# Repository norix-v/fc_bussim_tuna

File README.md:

# FC Cartridge bus simulator "tuna"

## What's it this?

This is famicom cartridge bus simulator 'kazzo' compatible hardware and extra software.  
The original project is [here](https://ja.osdn.net/projects/unagi/).  

## How to use

This data is provided "as is" and is freely available as long as you comply with the license.  
The author does not give an explanation or answer.  

## 何これ？

このプロジェクトはfamicom bus simulator 'kazzo' の互換のハードウェアとおまけのソフトウェアです。  
オリジナルのプロジェクトは[こちら](https://ja.osdn.net/projects/unagi/)です。  

## 使い方

このデータは"現状のまま"で提供され、ライセンスを遵守する限りにおいて自由に使用出来ます。なお、作者は説明も回答も致しませんのであしからず。

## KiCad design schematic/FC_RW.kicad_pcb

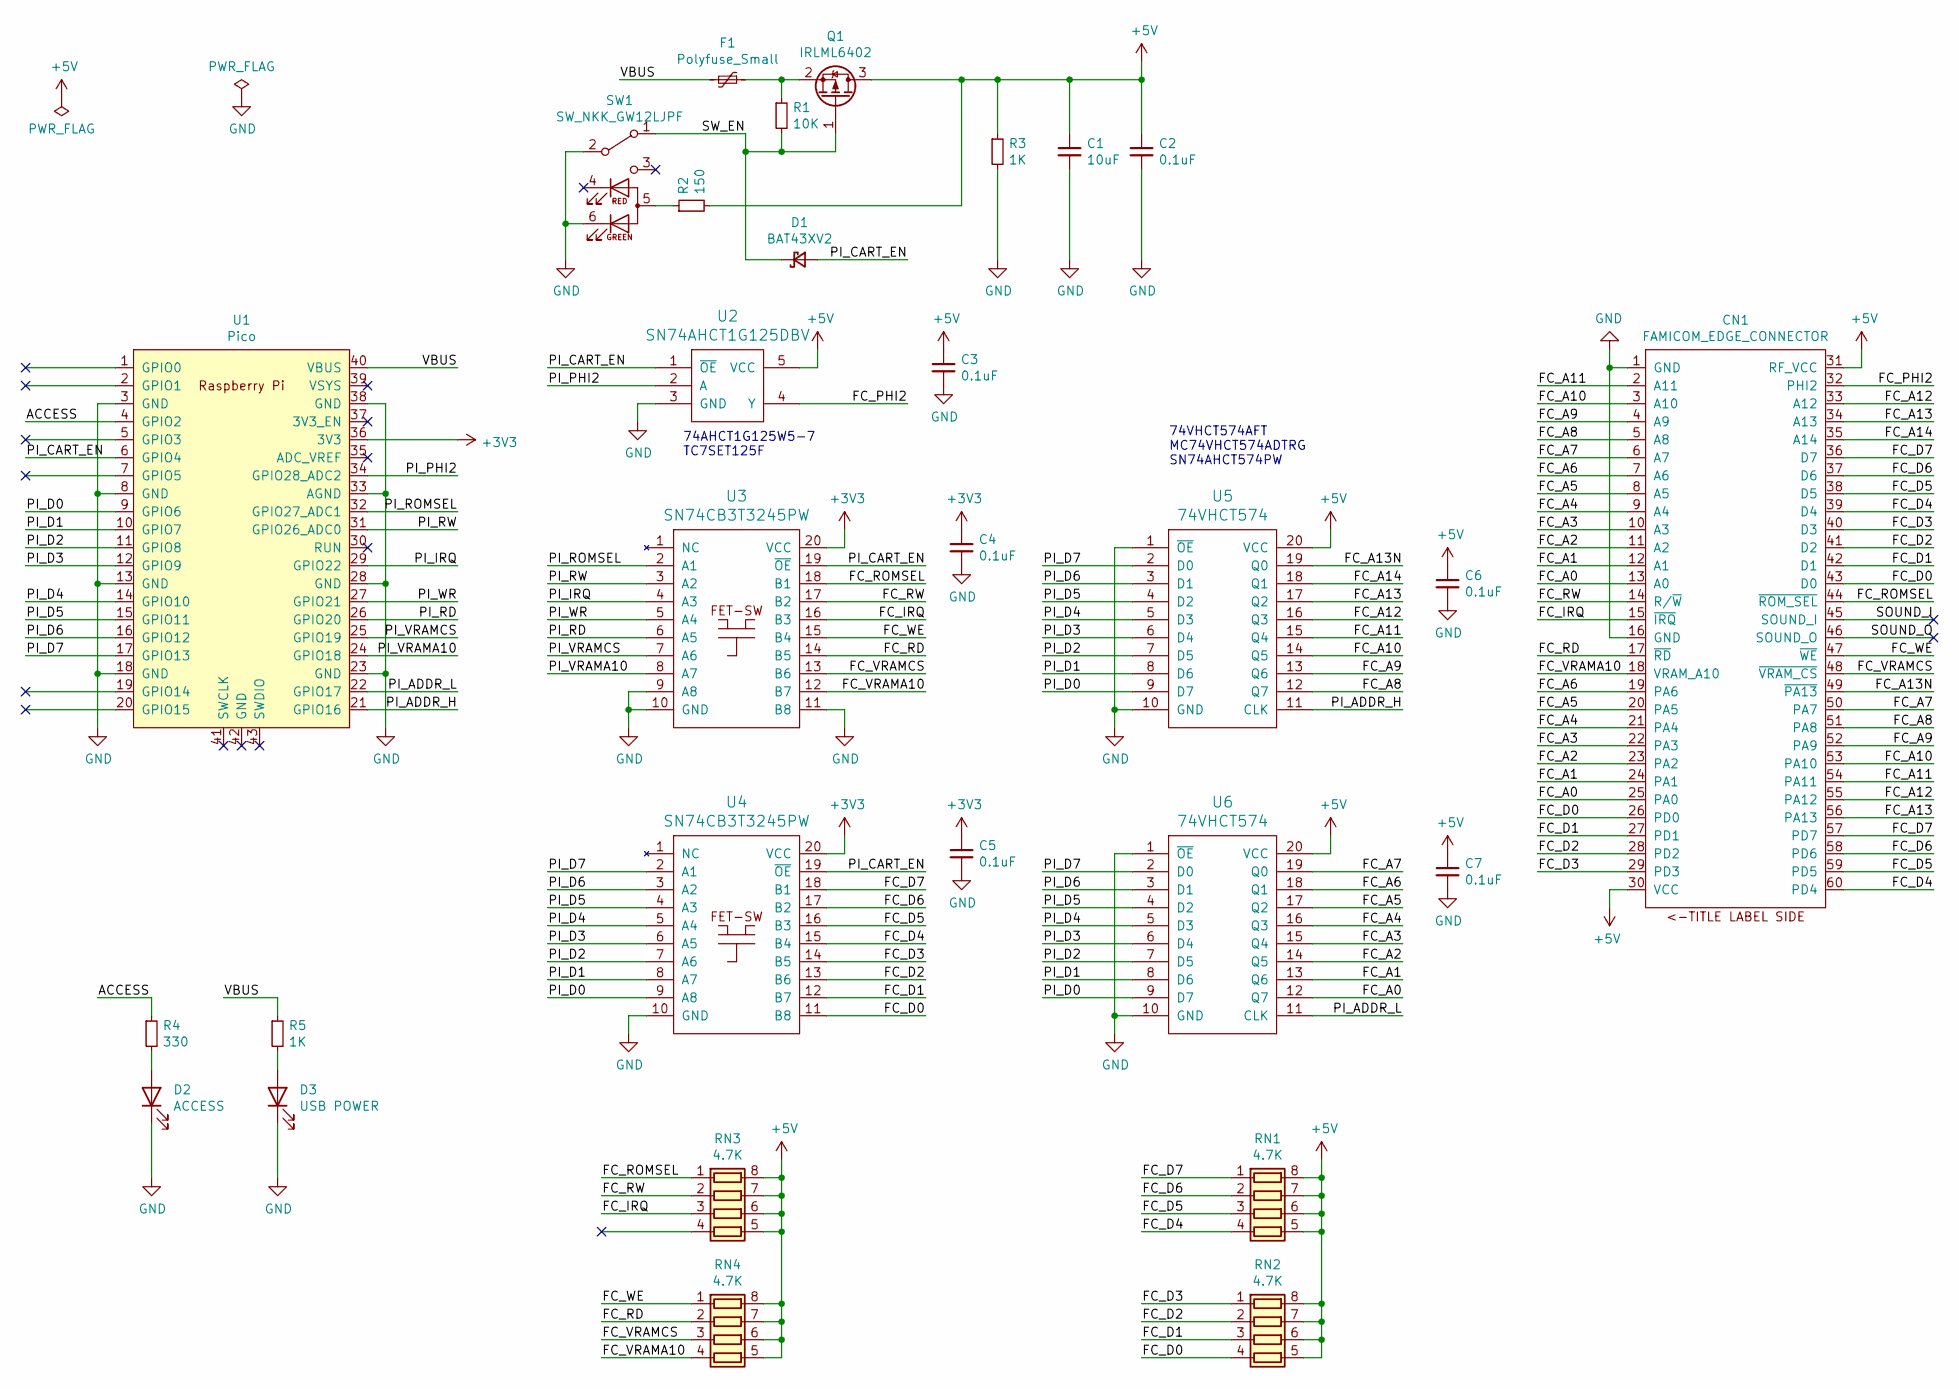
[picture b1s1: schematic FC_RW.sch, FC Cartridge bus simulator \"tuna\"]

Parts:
C1: 10uF; C_0805_2012Metric
C2, C3, C4, C5, C6, C7: 0.1uF; C_0603_1608Metric
CN1: FAMICOM_EDGE_CONNECTOR; Famicom_60pin
D1: BAT43XV2; D_SOD-523
D2: ACCESS; D_0805_2012Metric
D3: USB POWER; D_0805_2012Metric
F1: Polyfuse_Small; Fuse_0805_2012Metric
Q1: IRLML6402; SOT-23
R1: 10K; R_0603_1608Metric
R2: 150; R_0603_1608Metric
R3, R5: 1K; R_0603_1608Metric
R4: 330; R_0603_1608Metric
RN1, RN2, RN3, RN4: 4.7K; R_Array_Convex_4x0603
SW1: SW_NKK_GW12LJPF; SW_NKK_GW12LJP
U1: Pico; RPi_Pico_SMD_TH
U2: SN74AHCT1G125DBV; SOT-23-5
U3, U4: SN74CB3T3245PW; TSSOP-20_4.4x6.5mm_P0.65mm
U5, U6: 74VHCT574; TSSOP-20_4.4x6.5mm_P0.65mm

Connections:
+3V3: C4.1, C5.1, U1.36 (3V3), U3.20 (VCC), U4.20 (VCC)
+5V: C1.1, C2.1, C3.1, C6.1, C7.1, CN1.30 (VCC), CN1.31 (RF_VCC), Q1.3 (D), R2.2, R3.1, RN1.5 (R4.2), RN1.6 (R3.2), RN1.7 (R2.2), RN1.8 (R1.2), RN2.5 (R4.2), RN2.6 (R3.2), RN2.7 (R2.2), RN2.8 (R1.2), RN3.5 (R4.2), RN3.6 (R3.2), RN3.7 (R2.2), RN3.8 (R1.2), RN4.5 (R4.2), RN4.6 (R3.2), RN4.7 (R2.2), RN4.8 (R1.2), U2.5 (VCC), U5.20 (VCC), U6.20 (VCC)
/ACCESS: R4.1, U1.4 (GPIO2)
/FC_A0: CN1.13 (A0), CN1.25 (PA0), U6.12 (Q7)
/FC_A1: CN1.12 (A1), CN1.24 (PA1), U6.13 (Q6)
/FC_A2: CN1.11 (A2), CN1.23 (PA2), U6.14 (Q5)
/FC_A3: CN1.10 (A3), CN1.22 (PA3), U6.15 (Q4)
/FC_A4: CN1.9 (A4), CN1.21 (PA4), U6.16 (Q3)
/FC_A5: CN1.8 (A5), CN1.20 (PA5), U6.17 (Q2)
/FC_A6: CN1.7 (A6), CN1.19 (PA6), U6.18 (Q1)
/FC_A7: CN1.6 (A7), CN1.50 (PA7), U6.19 (Q0)
/FC_A8: CN1.5 (A8), CN1.51 (PA8), U5.12 (Q7)
/FC_A9: CN1.4 (A9), CN1.52 (PA9), U5.13 (Q6)
/FC_A10: CN1.3 (A10), CN1.53 (PA10), U5.14 (Q5)
/FC_A11: CN1.2 (A11), CN1.54 (PA11), U5.15 (Q4)
/FC_A12: CN1.33 (A12), CN1.55 (PA12), U5.16 (Q3)
/FC_A13: CN1.34 (A13), CN1.56 (PA13), U5.17 (Q2)
/FC_A13N: CN1.49 (~PA13), U5.19 (Q0)
/FC_A14: CN1.35 (A14), U5.18 (Q1)
/FC_D0: CN1.26 (PD0), CN1.43 (D0), RN2.4 (R4.1), U4.11 (B8)
/FC_D1: CN1.27 (PD1), CN1.42 (D1), RN2.3 (R3.1), U4.12 (B7)
/FC_D2: CN1.28 (PD2), CN1.41 (D2), RN2.2 (R2.1), U4.13 (B6)
/FC_D3: CN1.29 (PD3), CN1.40 (D3), RN2.1 (R1.1), U4.14 (B5)
/FC_D4: CN1.39 (D4), CN1.60 (PD4), RN1.4 (R4.1), U4.15 (B4)
/FC_D5: CN1.38 (D5), CN1.59 (PD5), RN1.3 (R3.1), U4.16 (B3)
/FC_D6: CN1.37 (D6), CN1.58 (PD6), RN1.2 (R2.1), U4.17 (B2)
/FC_D7: CN1.36 (D7), CN1.57 (PD7), RN1.1 (R1.1), U4.18 (B1)
/FC_IRQ: CN1.15 (~IRQ), RN3.3 (R3.1), U3.16 (B3)
/FC_PHI2: CN1.32 (PHI2), U2.4 (Y)
/FC_RD: CN1.17 (~RD), RN4.2 (R2.1), U3.14 (B5)
/FC_ROMSEL: CN1.44 (~ROM_SEL), RN3.1 (R1.1), U3.18 (B1)
/FC_RW: CN1.14 (R/~W), RN3.2 (R2.1), U3.17 (B2)
/FC_VRAMA10: CN1.18 (VRAM_A10), RN4.4 (R4.1), U3.12 (B7)
/FC_VRAMCS: CN1.48 (~VRAM_CS), RN4.3 (R3.1), U3.13 (B6)
/FC_WE: CN1.47 (~WE), RN4.1 (R1.1), U3.15 (B4)
/PI_ADDR_H: U1.21 (GPIO16), U5.11 (CLK)
/PI_ADDR_L: U1.22 (GPIO17), U6.11 (CLK)
/PI_CART_EN: D1.2 (A), U1.6 (GPIO4), U2.1 (~OE), U3.19 (~OE), U4.19 (~OE)
/PI_D0: U1.9 (GPIO6), U4.9 (A8), U5.9 (D7), U6.9 (D7)
/PI_D1: U1.10 (GPIO7), U4.8 (A7), U5.8 (D6), U6.8 (D6)
/PI_D2: U1.11 (GPIO8), U4.7 (A6), U5.7 (D5), U6.7 (D5)
/PI_D3: U1.12 (GPIO9), U4.6 (A5), U5.6 (D4), U6.6 (D4)
/PI_D4: U1.14 (GPIO10), U4.5 (A4), U5.5 (D3), U6.5 (D3)
/PI_D5: U1.15 (GPIO11), U4.4 (A3), U5.4 (D2), U6.4 (D2)
/PI_D6: U1.16 (GPIO12), U4.3 (A2), U5.3 (D1), U6.3 (D1)
/PI_D7: U1.17 (GPIO13), U4.2 (A1), U5.2 (D0), U6.2 (D0)
/PI_IRQ: U1.29 (GPIO22), U3.4 (A3)
/PI_PHI2: U1.34 (GPIO28_ADC2), U2.2 (A)
/PI_RD: U1.26 (GPIO20), U3.6 (A5)
/PI_ROMSEL: U1.32 (GPIO27_ADC1), U3.2 (A1)
/PI_RW: U1.31 (GPIO26_ADC0), U3.3 (A2)
/PI_VRAMA10: U1.24 (GPIO18), U3.8 (A7)
/PI_VRAMCS: U1.25 (GPIO19), U3.7 (A6)
/PI_WR: U1.27 (GPIO21), U3.5 (A4)
/SOUND_I: CN1.45 (SOUND_I)
/SOUND_O: CN1.46 (SOUND_O)
/SW_EN: D1.1 (K), Q1.1 (G), R1.2, SW1.1 (A)
/VBUS: F1.2, R5.1, U1.40 (VBUS)
GND: C1.2, C2.2, C3.2, C4.2, C5.2, C6.2, C7.2, CN1.1 (GND), CN1.16 (GND), D2.1 (K), D3.1 (K), R3.2, SW1.2 (B), SW1.6 (KG), U1.3 (GND), U1.8 (GND), U1.13 (GND), U1.18 (GND), U1.23 (GND), U1.28 (GND), U1.33 (AGND), U1.38 (GND), U2.3 (GND), U3.9 (A8), U3.10 (GND), U3.11 (B8), U4.10 (GND), U5.1 (~OE), U5.10 (GND), U6.1 (~OE), U6.10 (GND)
unnamed: D2.2 (A), R4.2
unnamed: D3.2 (A), R5.2
unnamed: F1.1, Q1.2 (S), R1.1
unnamed: R2.1, SW1.5 (A)

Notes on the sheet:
74VHCT574AFT MC74VHCT574ADTRG SN74AHCT574PW
74AHCT1G125W5-7 TC7SET125F

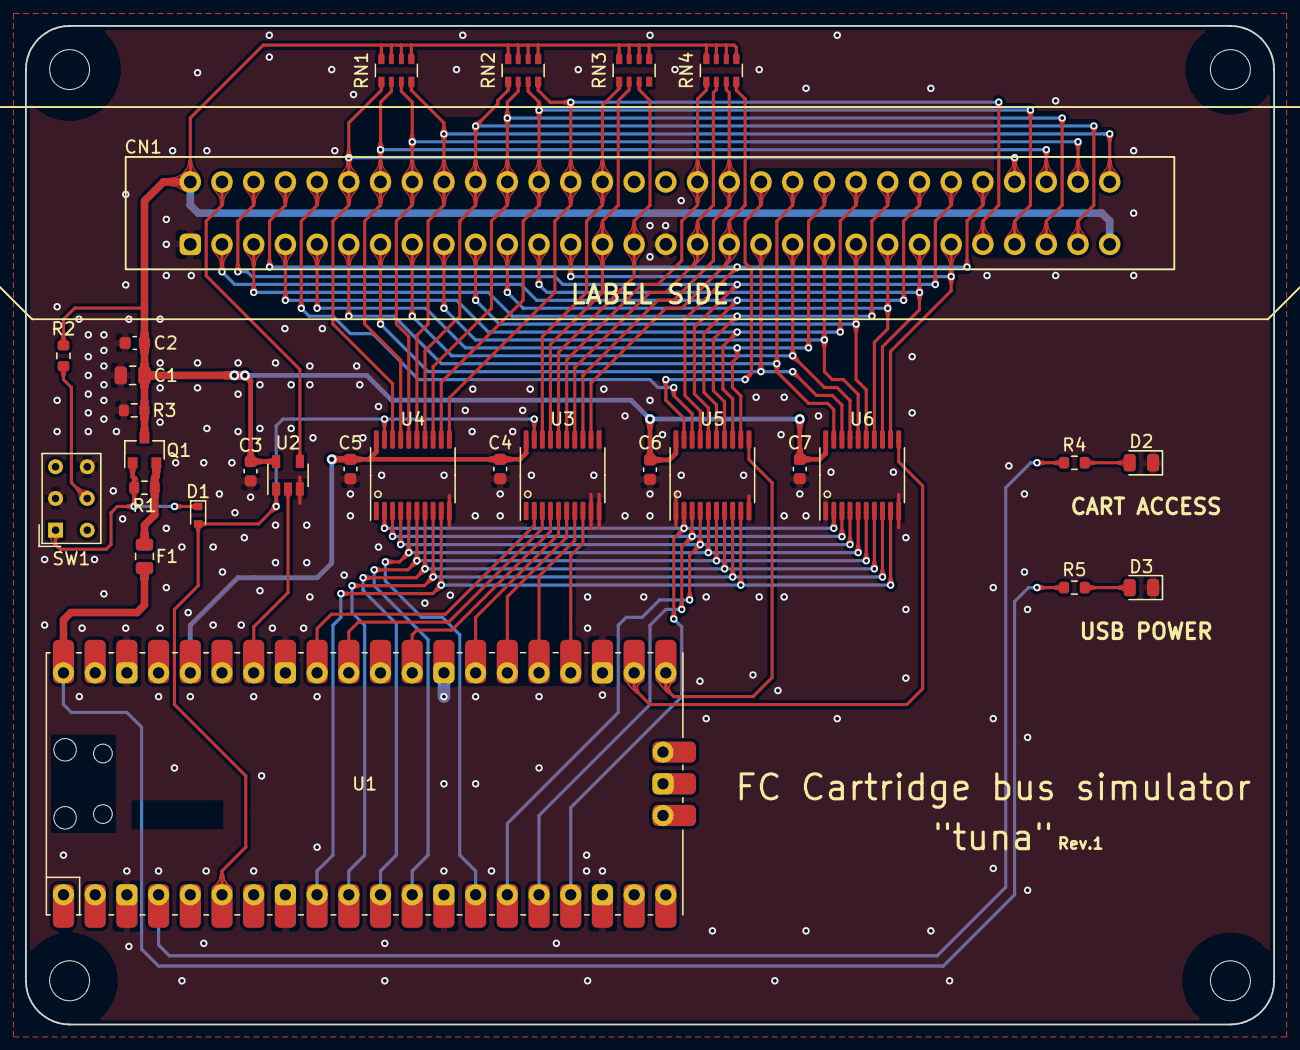
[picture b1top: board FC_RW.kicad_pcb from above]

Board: 2 copper layers, 100.0 x 80.0 mm, 29 parts (0 on the bottom side), 61 nets.

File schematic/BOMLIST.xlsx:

FC Cartridge bus simulator “tuna” BOM list
Reference | Qty | Value | Name | Package type | Note
C1 | 1 | 10uF | 10uF | 0805/2012 | Any manufacturer. Rated voltage should be 6.3V or higher.
C2,C3,C4,C5,C6,C7 | 6 | 0.1uF | 0.1uF | 0603/1608 | Any manufacturer. Rated voltage should be 6.3V or higher.
CN1 | 1 | FAMICOM_EDGE_CONNECTOR | 5530843-7 (TE Connectivity) CR22A-60D-2.54DS(70) (HIROSE) | Through hole | Card edge connector 2.54mm(0.1inch) pitch 60pins.
D1 | 1 | BAT43XV2 | BAT43VX2 (ON semiconductor) | SOD-523 | Any manufacturer with similar specifications.
D2 | 1 | ACCESS | OSO50805C1C (OptoSupply, Orange) | 0805/2012 | Any color, any manufacturer.
D3 | 1 | USB POWER | OSR50805C1C (OptoSupply, Red) | 0805/2012 | Any color, any manufacturer.
F1 | 1 | Polyfuse_Small | MF-PSMF020X-2 (Bourns) | 0805/2012 | Hold 200mA, Trip at 500mA. Any similar specifications.
Q1 | 1 | IRLML6402 | Pch MOSFET IRLML6402 | SOT-23 | Any manufacturer with similar specifications.
R1 | 1 | 10K | 10K ohm | 0603/1608 | Any manufacturer.
R2 | 1 | 150 | 150 ohm | 0603/1608 | Any manufacturer.
R3,R5 | 2 | 1K | 1K ohm | 0603/1608 | Any manufacturer.
R4 | 1 | 330 | 330 ohm | 0603/1608 | Any manufacturer.
RN1,RN2,RN3,RN4 | 4 | 4.7K | CAY16A-471J4LF (Bourns) | 4x0603 | Any manufacturer.
SW1 | 1 | SW_NKK_GW12LJPF | GW12LJPF (NKK Switches) | Through hole | Any like color.
U1 | 1 | Pico | Rasiberry Pi Pico RP2040 | SMD | The Raspberry Pi Foundation product.
U2 | 1 | SN74AHCT1G125DBV | Buffer | SOT-23-5 | Any manufacturer with similar specifications. TTL level input and input power d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
U3,U4 | 2 | SN74CB3T3245PW | 8-channel FET bus switch with level shifter | TSSOP-20_4.4x6.5mm_P0.65mm | Texas Instruments Inc. only.
U5,U6 | 2 | 74VHCT574 | Octal flip flop | TSSOP-20_4.4x6.5mm_P0.65mm | Any manufacturer with similar specifications. TTL level input and input power d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
Note: This BOM lists the ones used by the author. Compatible products exist for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

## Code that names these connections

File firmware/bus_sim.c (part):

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// pin definitions
// output pins
#define	PI_PHI2_BIT		28
#define	PI_PHI2			(1<<PI_PHI2_BIT)
#define	PI_ROMSEL_BIT	27
#define	PI_ROMSEL		(1<<PI_ROMSEL_BIT)
#define	PI_RW_BIT		26
#define	PI_RW			(1<<PI_RW_BIT)
#define	PI_WR_BIT		21
#define	PI_WR			(1<<PI_WR_BIT)
#define	PI_RD_BIT		20
#define	PI_RD			(1<<PI_RD_BIT)

#define	PI_ADDR_L_BIT	17
#define	PI_ADDR_L		(1<<PI_ADDR_L_BIT)
#define	PI_ADDR_H_BIT	16
#define	PI_ADDR_H		(1<<PI_ADDR_H_BIT)

// inout pins
#define	PI_CART_ENABLE_BIT	4
#define	PI_CART_ENABLE	(1<<PI_CART_ENABLE_BIT)
#define	PI_IRQ_BIT		22
#define	PI_IRQ			(1<<PI_IRQ_BIT)
#define	PI_VRAMCS_BIT	19
#define	PI_VRAMCS		(1<<PI_VRAMCS_BIT)
#define	PI_VRAMA10_BIT	18
#define	PI_VRAMA10		(1<<PI_VRAMA10_BIT)

// bi-directional pins
#define	PI_D7_BIT		13
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#define	PI_ACCESS_BIT	2
#define	PI_ACCESS		(1<<PI_ACCESS_BIT)

#define	PI_OUT_PINS		(PI_PHI2|PI_ROMSEL|PI_RW|PI_WR|PI_RD|PI_ADDR_L|PI_ADDR_H|PI_ACCESS)
#define	PI_INP_PINS		(PI_CART_ENABLE|PI_IRQ|PI_VRAMCS|PI_VRAMA10)
#define	PI_BIDIR_PINS	(PI_DATA_MASK)

// bussim access types
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
	// cpu bus control pins to 'L'
	gpio_init_mask(PI_OUT_PINS);
	gpio_put_masked(PI_OUT_PINS, PI_RD|PI_WR);
	gpio_set_dir_out_masked(PI_OUT_PINS);
}

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
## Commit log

2021-04-16 Fixed cpu (ppu) _write_flash not to skip $FF.
2022-01-31 fix BOM list

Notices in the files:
firmware/bus_sim.c:
Copyrighte (C) 2021 Norix (NX labs)
License: GPL2 (see gpl-2.0.txt)
